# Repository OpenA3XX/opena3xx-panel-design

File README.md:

# 🛫 OpenA3XX: Panels, 3D Printed Components & Reference Archive
Welcome to the central repository for the OpenA3XX **Airbus cockpit build project**! This repository documents the design, construction, and references for all the cockpit panels and components, including 3D printed parts and photographic material used during development.

---

---

## ✈️ About the Project

As part of a long-term flight simulation setup, I'm building a **home Airbus cockpit replica**, focusing on authenticity, durability, and modularity. This project includes:

- Accurate panel layouts (e.g., ADIRS, FLT-CTL, etc.)
- Reference imagery from real cockpits
- 3D printed components (knobs, switch housings, structural parts)
- Design schematics, templates, and notes from real-world dimensions
- Documentation of tools and techniques used in building panels

This repository serves as a **knowledge base** and a **design vault** for other sim builders and enthusiasts who are building or planning to build their own Airbus home cockpit.

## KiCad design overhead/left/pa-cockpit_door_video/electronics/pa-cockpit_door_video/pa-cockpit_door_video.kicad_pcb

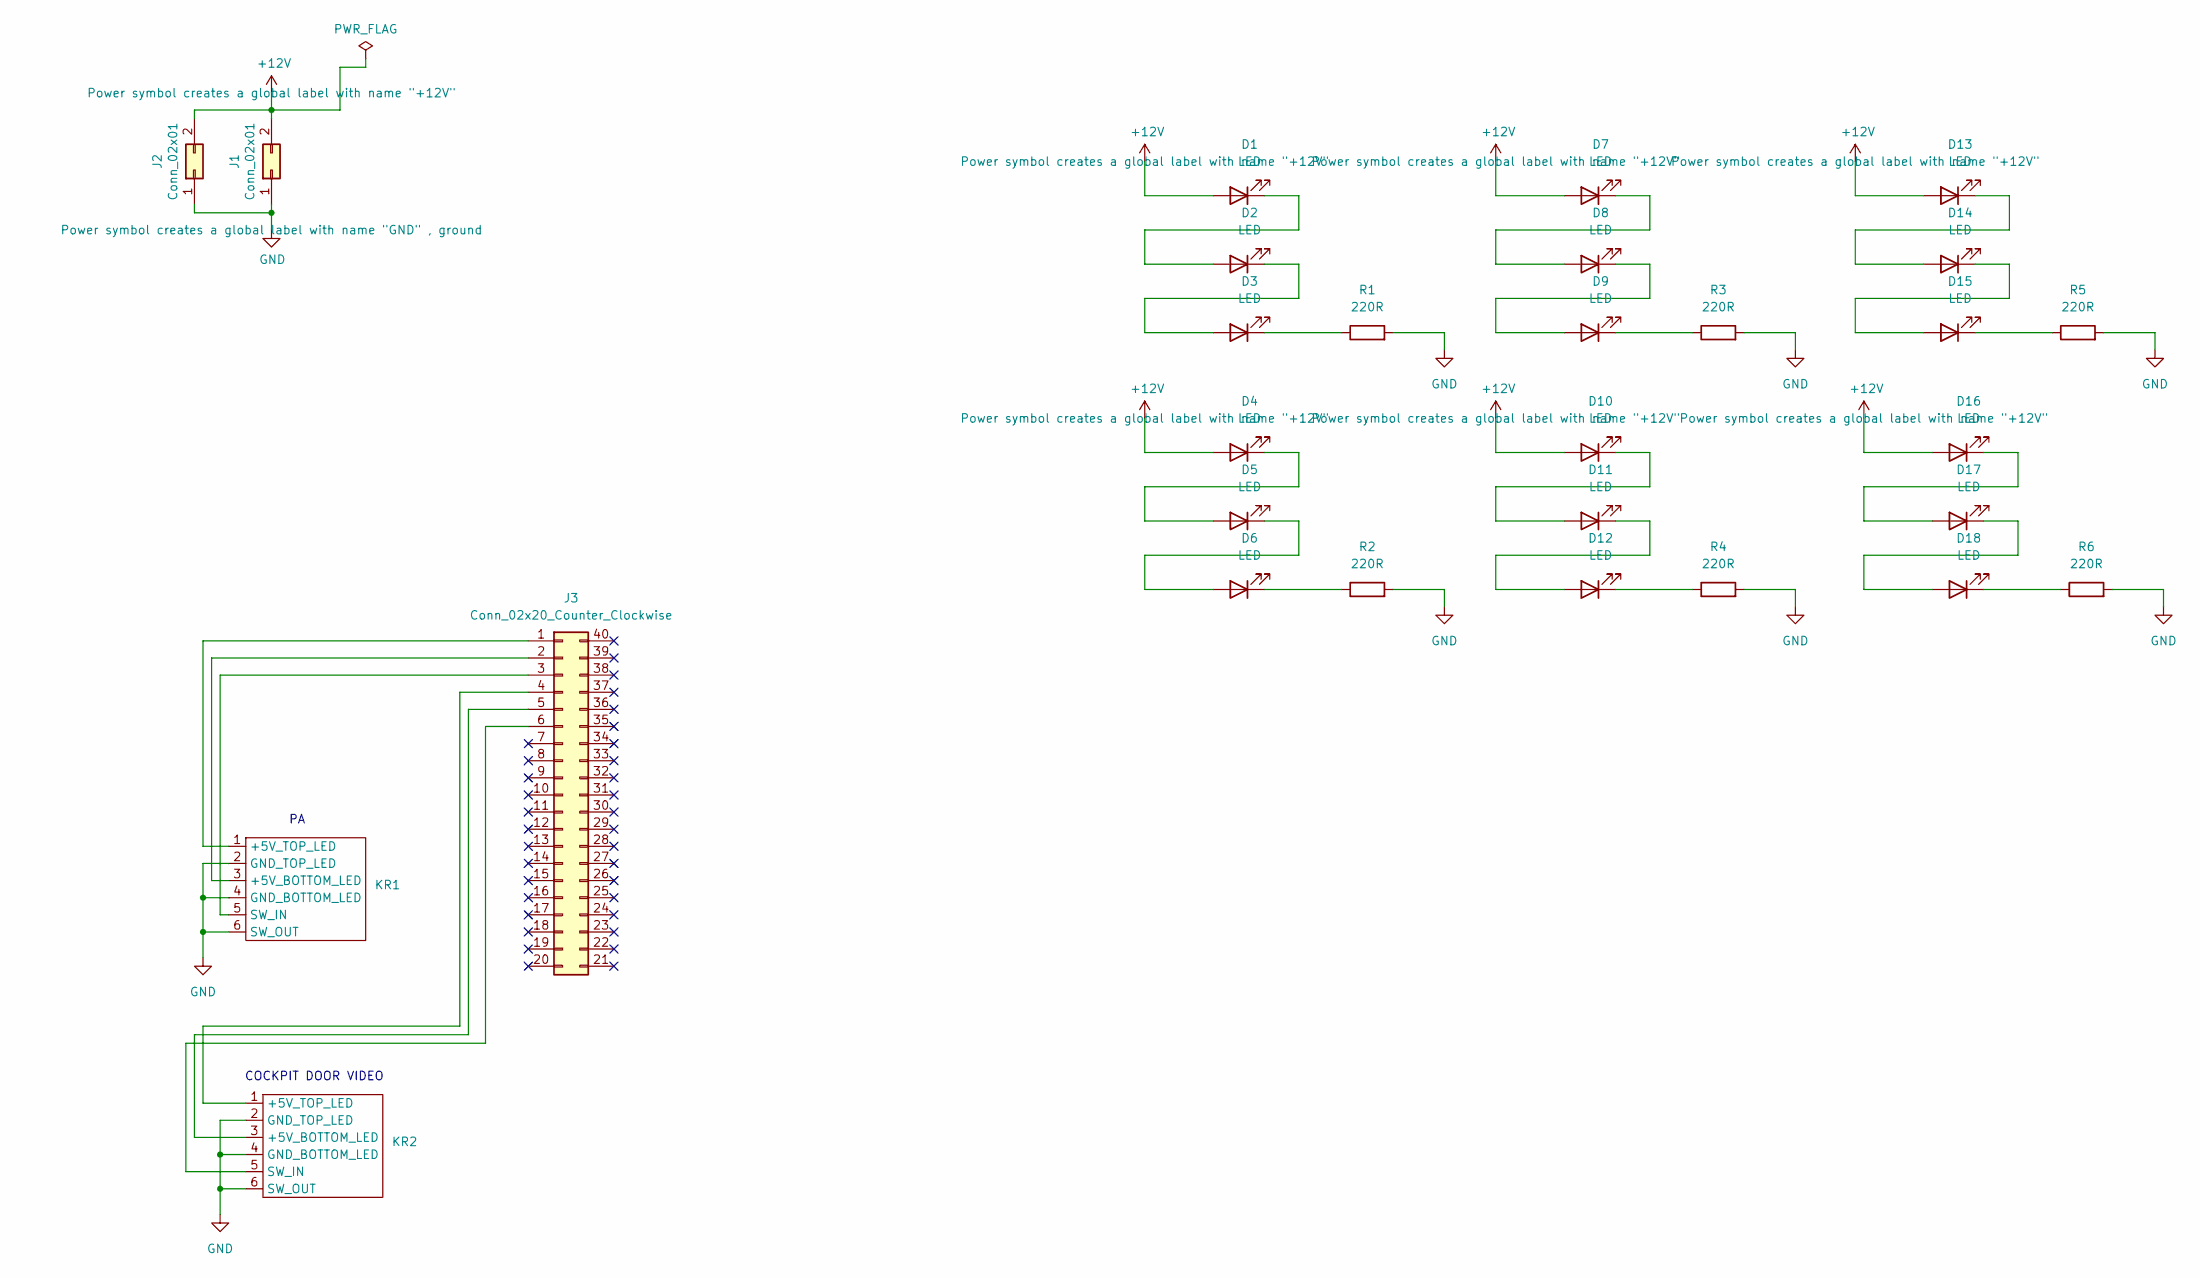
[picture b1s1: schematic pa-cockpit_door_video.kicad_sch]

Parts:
D1, D2, D3, D4, D5, D6, D7, D8, D9, D10, D11, D12, D13, D14, D15, D16, D17, D18: LED; LED_Everlight-SMD3528_3.5x2.8mm_67-21ST
J1, J2: Conn_02x01; TerminalBlock_bornier-2_P5.08mm
J3: Conn_02x20_Counter_Clockwise; PinHeader_2x20_P2.54mm_Vertical
KR1, KR2: Korry Switch
R1, R2, R3, R4, R5, R6: 220R; R_1206_3216Metric_Pad1.30x1.75mm_HandSolder

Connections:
+12V: D1.2 (A), D4.2 (A), D7.2 (A), D10.2 (A), D13.2 (A), D16.2 (A), J1.2, J2.2
GND: J1.1, J2.1, KR1.2 (GND_TOP_LED), KR1.4 (GND_BOTTOM_LED), KR1.6 (SW_OUT), KR2.2 (GND_TOP_LED), KR2.4 (GND_BOTTOM_LED), KR2.6 (SW_OUT), R1.2, R2.2, R3.2, R4.2, R5.2, R6.2
unnamed: D1.1 (K), D2.2 (A)
unnamed: D2.1 (K), D3.2 (A)
unnamed: D3.1 (K), R1.1
unnamed: D4.1 (K), D5.2 (A)
unnamed: D5.1 (K), D6.2 (A)
unnamed: D6.1 (K), R2.1
unnamed: D7.1 (K), D8.2 (A)
unnamed: D8.1 (K), D9.2 (A)
unnamed: D9.1 (K), R3.1
unnamed: D10.1 (K), D11.2 (A)
unnamed: D11.1 (K), D12.2 (A)
unnamed: D12.1 (K), R4.1
unnamed: D13.1 (K), D14.2 (A)
unnamed: D14.1 (K), D15.2 (A)
unnamed: D15.1 (K), R5.1
unnamed: D16.1 (K), D17.2 (A)
unnamed: D17.1 (K), D18.2 (A)
unnamed: D18.1 (K), R6.1
unnamed: J3.1, KR1.1 (+5V_TOP_LED)
unnamed: J3.2, KR1.3 (+5V_BOTTOM_LED)
unnamed: J3.3, KR1.5 (SW_IN)
unnamed: J3.4, KR2.1 (+5V_TOP_LED)
unnamed: J3.5, KR2.3 (+5V_BOTTOM_LED)
unnamed: J3.6, KR2.5 (SW_IN)

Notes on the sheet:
COCKPIT DOOR VIDEO

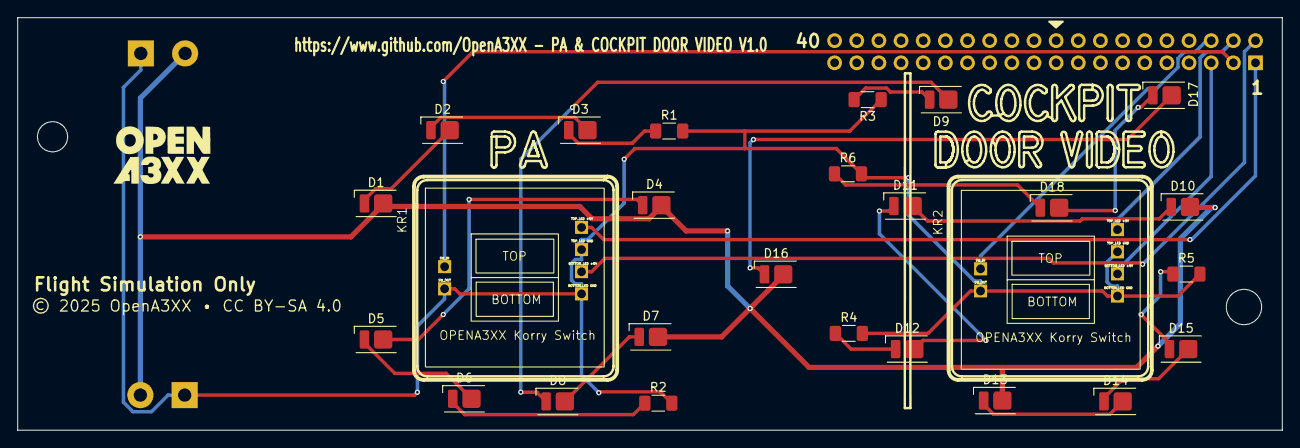
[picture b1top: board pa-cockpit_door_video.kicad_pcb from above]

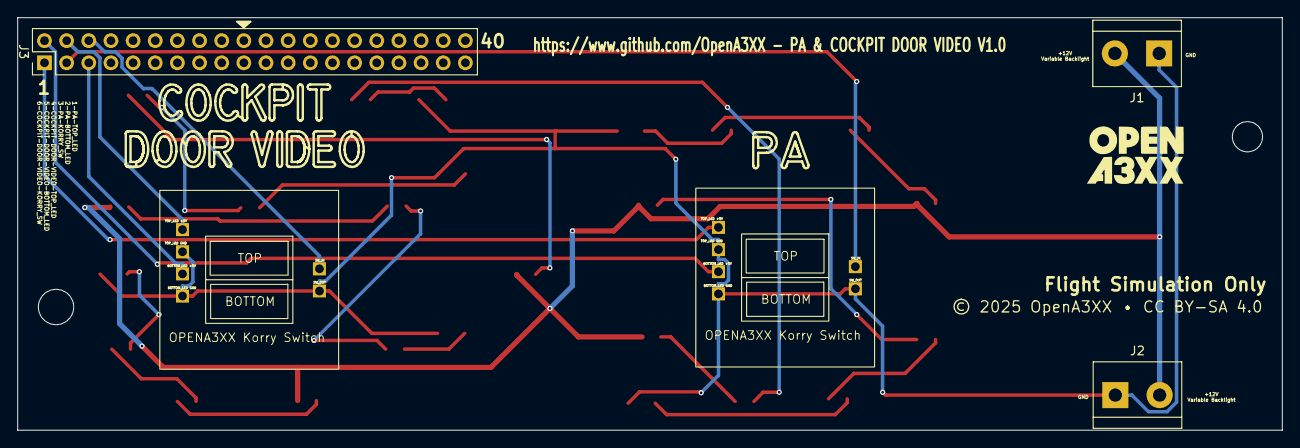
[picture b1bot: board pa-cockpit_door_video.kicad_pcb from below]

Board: 2 copper layers, 145.0 x 47.3 mm, 31 parts (4 on the bottom side), 26 nets.

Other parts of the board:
bottom: LOGO; OpenA3XXLogoSmall
top: LOGO; OpenA3XXLogoSmall

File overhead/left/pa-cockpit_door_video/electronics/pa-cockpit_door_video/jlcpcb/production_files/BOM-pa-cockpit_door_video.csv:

Comment,Designator,Footprint,LCSC,Quantity
LED,"D1,D10,D11,D12,D13,D14,D15,D16,D17,D18,D2,D3,D4,D5,D6,D7,D8,D9",LED_Everlight-SMD3528_3.5x2.8mm_67-21ST,C2843803,18
220R,"R1,R2,R3,R4,R5,R6",R_1206_3216Metric_Pad1.30x1.75mm_HandSolder,C2933785,6
Conn_02x01,"J1,J2",TerminalBlock_bornier-2_P5.08mm,C592976,2
Conn_02x20_Counter_Clockwise,J3,PinHeader_2x20_P2.54mm_Vertical,C725892,1
~,KR2,Korry Switch,,1
~,KR1,Korry Switch,,1

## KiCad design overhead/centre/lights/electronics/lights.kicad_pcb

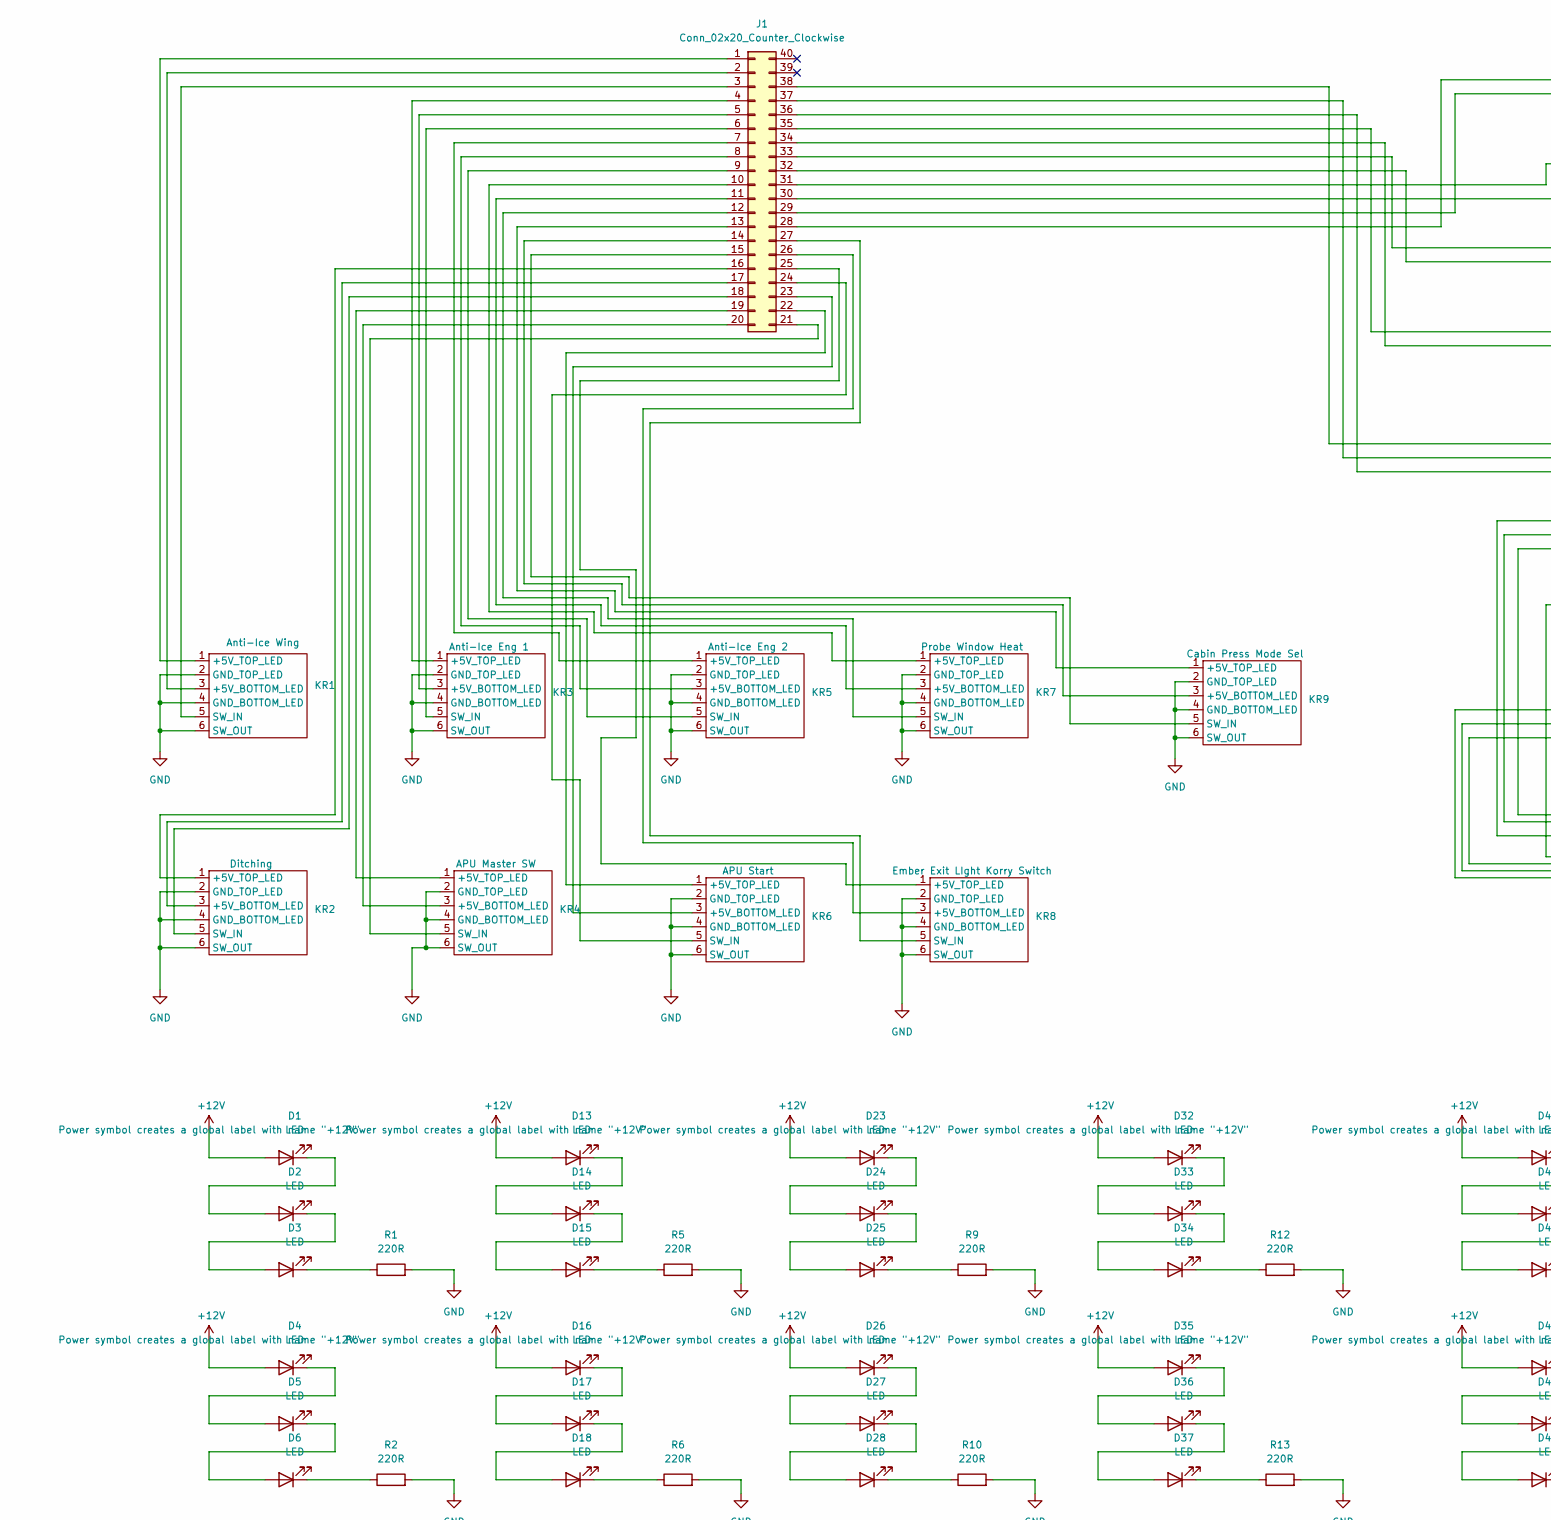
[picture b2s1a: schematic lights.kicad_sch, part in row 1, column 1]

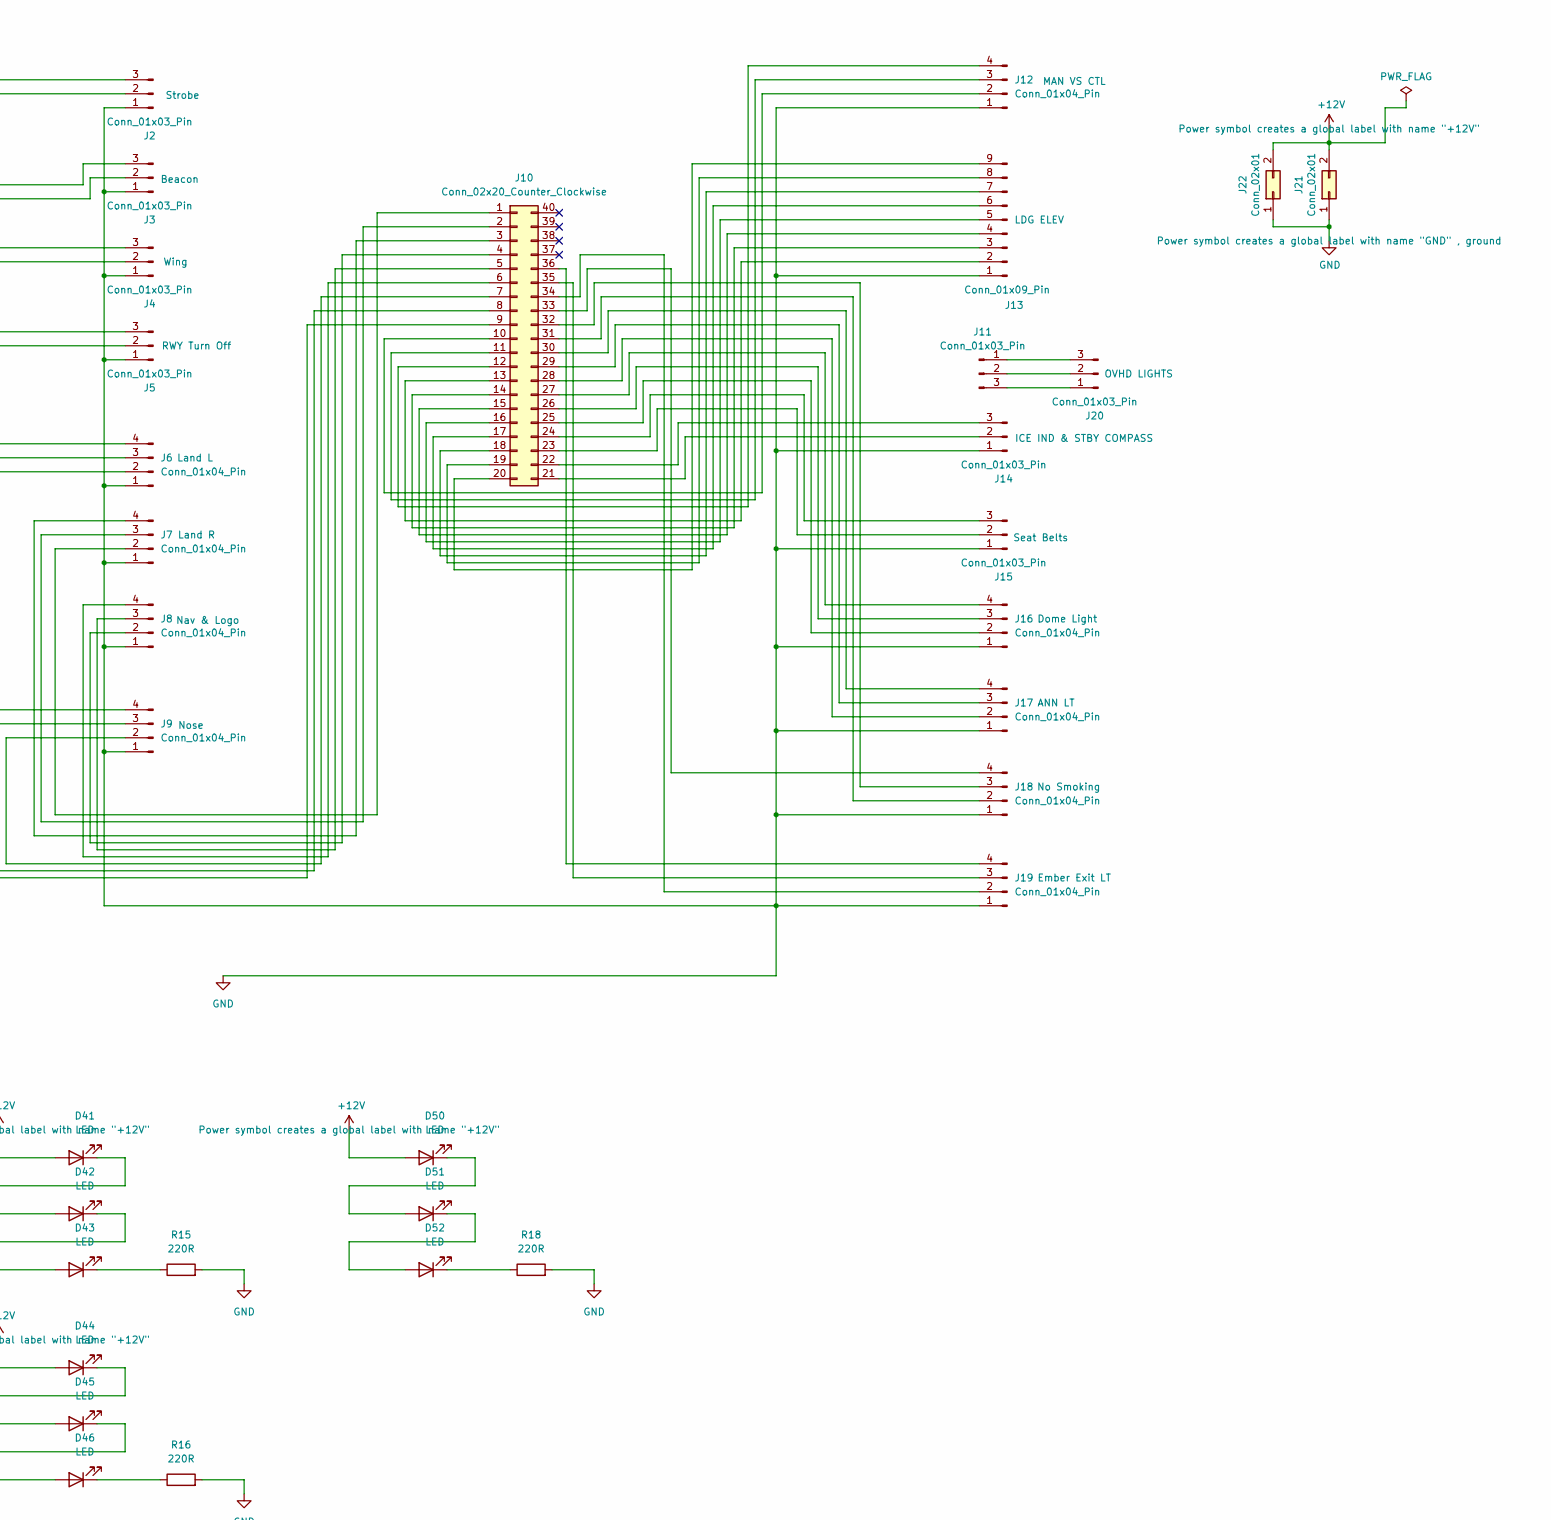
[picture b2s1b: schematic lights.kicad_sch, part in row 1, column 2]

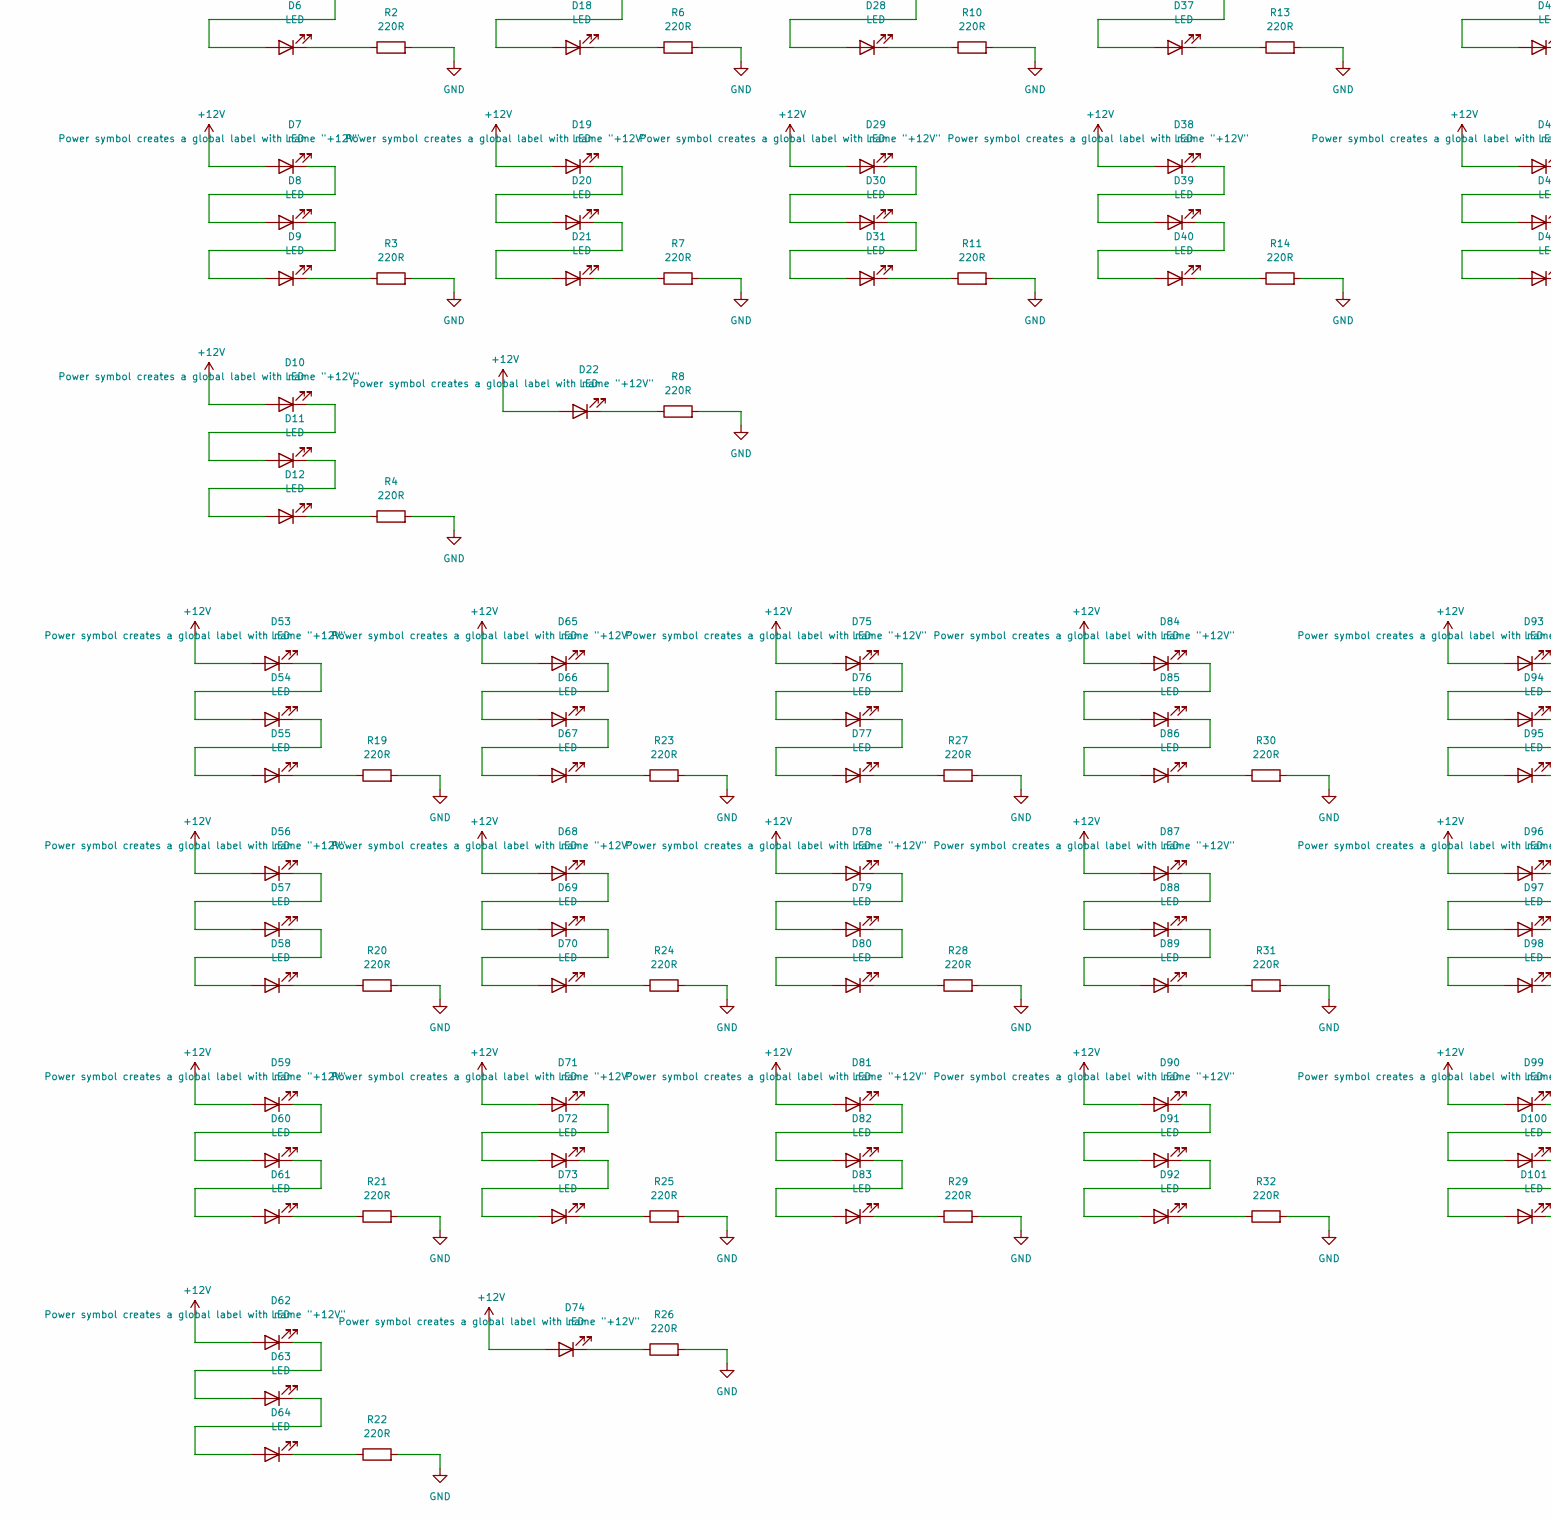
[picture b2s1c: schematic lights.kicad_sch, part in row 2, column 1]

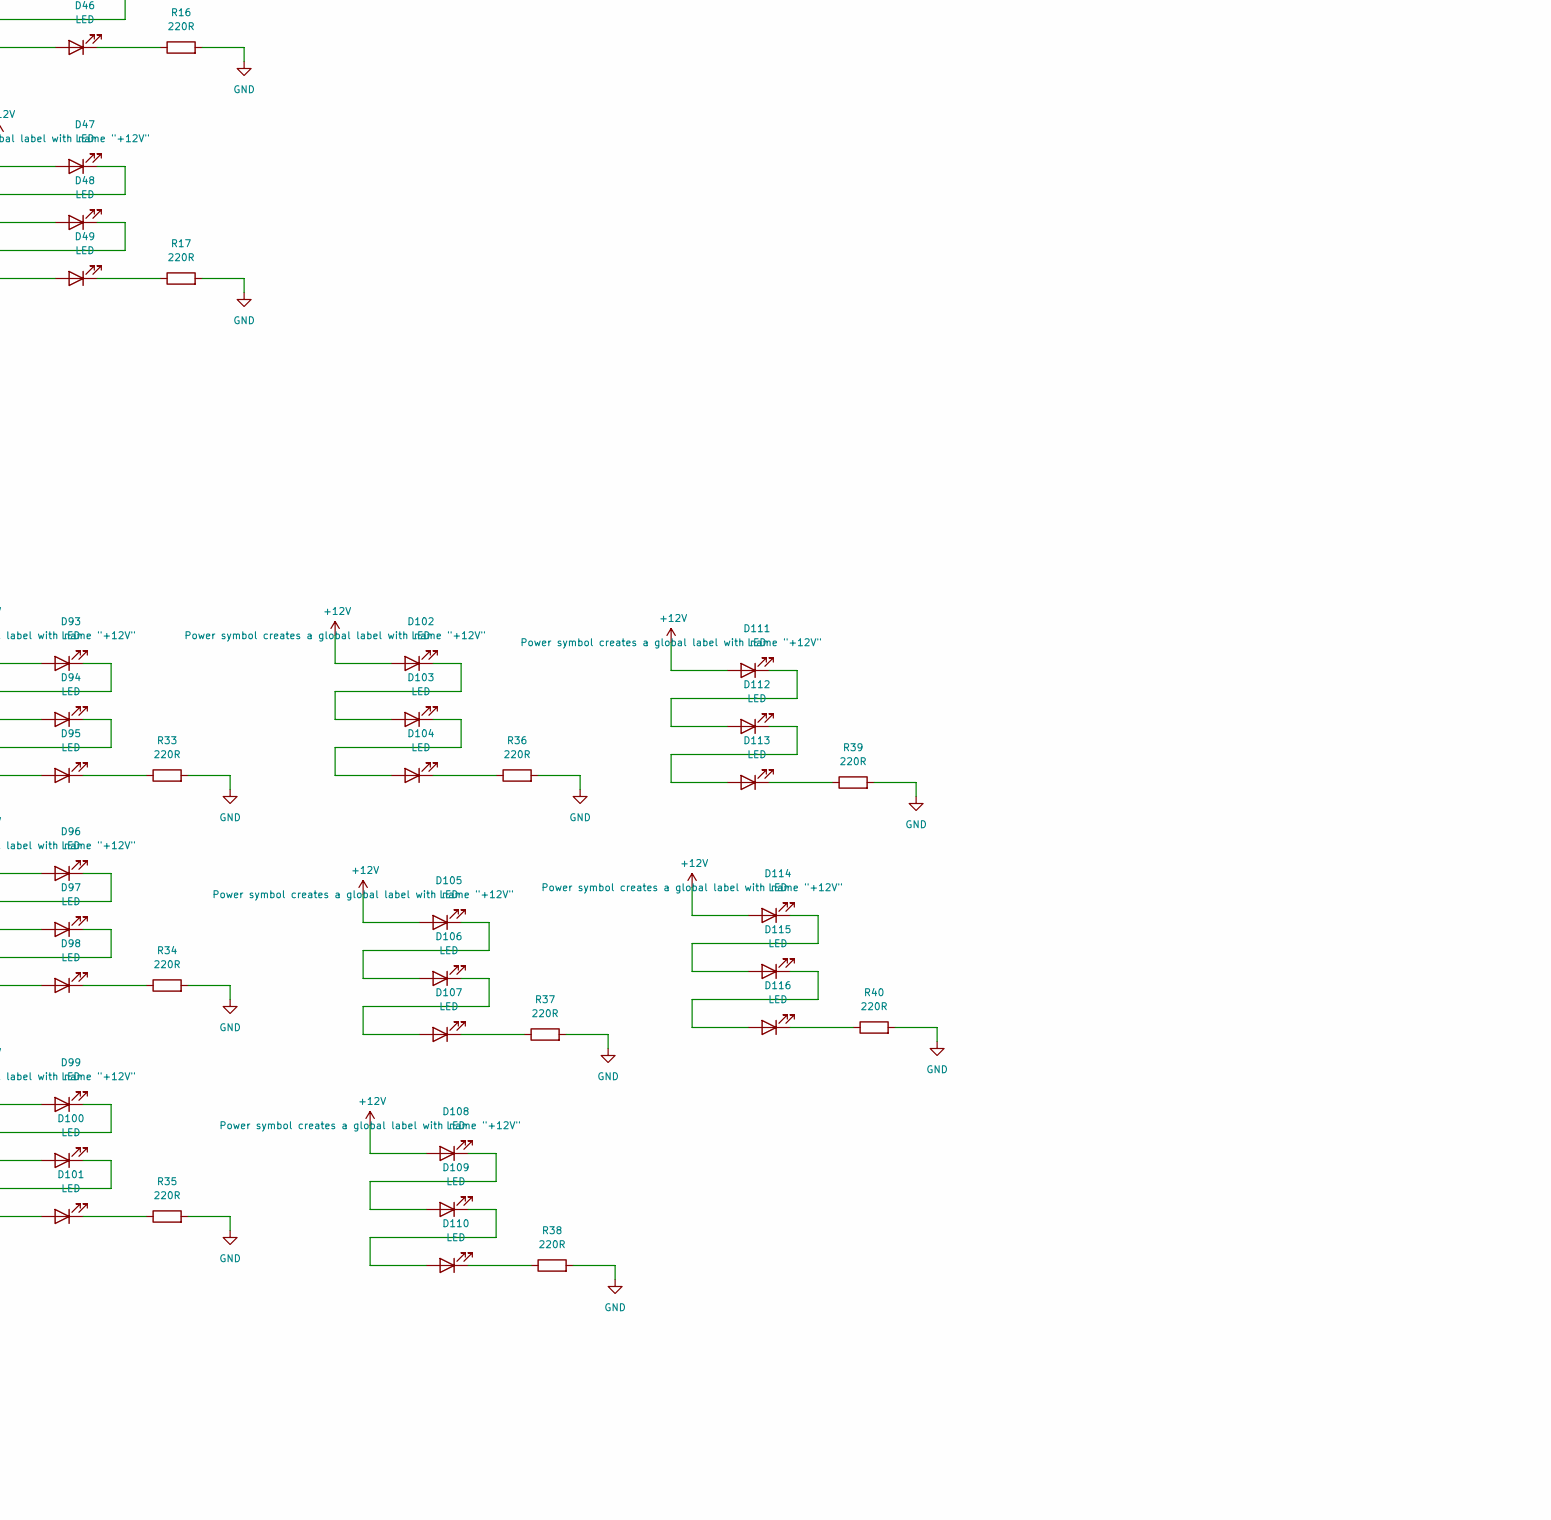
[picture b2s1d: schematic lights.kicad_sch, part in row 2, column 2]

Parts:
D1, D2, D3, D4, D5, D6, D7, D8, D9, D10, D11, D12, D13, D14, D15, D16, D17, D18, D19, D20, D21, D22, D23, D24, D25, D26, D27, D28, D29, D30, D31, D32, D33, D34, D35, D36, D37, D38, D39, D40, D41, D42, D43, D44, D45, D46, D47, D48, D49, D50, D51, D52, D53, D54, D55, D56, D57, D58, D59, D60, D61, D62, D63, D64, D65, D66, D67, D68, D69, D70, D71, D72, D73, D74, D75, D76, D77, D78, D79, D80, D81, D82, D83, D84, D85, D86, D87, D88, D89, D90, D91, D92, D93, D94, D95, D96, D97, D98, D99, D100, D101, D102, D103, D104, D105, D106, D107, D108, D109, D110, D111, D112, D113, D114, D115, D116: LED; LED_Everlight-SMD3528_3.5x2.8mm_67-21ST
J1, J10: Conn_02x20_Counter_Clockwise; PinHeader_2x20_P2.54mm_Vertical
J2, J3, J4, J5, J11, J14, J15: Conn_01x03_Pin; PinHeader_1x03_P2.54mm_Vertical
J6, J7, J8, J9, J12, J16, J17, J18, J19: Conn_01x04_Pin; PinHeader_1x04_P2.54mm_Vertical
J13: Conn_01x09_Pin; PinHeader_1x09_P2.54mm_Vertical
J20: Conn_01x03_Pin; TerminalBlock_bornier-3_P5.08mm
J21, J22: Conn_02x01; TerminalBlock_bornier-2_P5.08mm
KR1, KR2, KR3, KR4, KR5, KR6, KR7, KR8, KR9: Korry Switch
R1, R2, R3, R4, R5, R6, R7, R8, R9, R10, R11, R12, R13, R14, R15, R16, R17, R18, R19, R20, R21, R22, R23, R24, R25, R26, R27, R28, R29, R30, R31, R32, R33, R34, R35, R36, R37, R38, R39, R40: 220R; R_1206_3216Metric_Pad1.30x1.75mm_HandSolder

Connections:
+12V: D1.2 (A), D4.2 (A), D7.2 (A), D10.2 (A), D13.2 (A), D16.2 (A), D19.2 (A), D22.2 (A), D23.2 (A), D26.2 (A), D29.2 (A), D32.2 (A), D35.2 (A), D38.2 (A), D41.2 (A), D44.2 (A), D47.2 (A), D50.2 (A), D53.2 (A), D56.2 (A), D59.2 (A), D62.2 (A), D65.2 (A), D68.2 (A), D71.2 (A), D74.2 (A), D75.2 (A), D78.2 (A), D81.2 (A), D84.2 (A), D87.2 (A), D90.2 (A), D93.2 (A), D96.2 (A), D99.2 (A), D102.2 (A), D105.2 (A), D108.2 (A), D111.2 (A), D114.2 (A), J21.2, J22.2
GND: J2.1, J3.1, J4.1, J5.1, J6.1, J7.1, J8.1, J9.1, J12.1, J13.1, J14.1, J15.1, J16.1, J17.1, J18.1, J19.1, J21.1, J22.1, KR1.2 (GND_TOP_LED), KR1.4 (GND_BOTTOM_LED), KR1.6 (SW_OUT), KR2.2 (GND_TOP_LED), KR2.4 (GND_BOTTOM_LED), KR2.6 (SW_OUT), KR3.2 (GND_TOP_LED), KR3.4 (GND_BOTTOM_LED), KR3.6 (SW_OUT), KR4.2 (GND_TOP_LED), KR4.4 (GND_BOTTOM_LED), KR4.6 (SW_OUT), KR5.2 (GND_TOP_LED), KR5.4 (GND_BOTTOM_LED), KR5.6 (SW_OUT), KR6.2 (GND_TOP_LED), KR6.4 (GND_BOTTOM_LED), KR6.6 (SW_OUT), KR7.2 (GND_TOP_LED), KR7.4 (GND_BOTTOM_LED), KR7.6 (SW_OUT), KR8.2 (GND_TOP_LED), KR8.4 (GND_BOTTOM_LED), KR8.6 (SW_OUT), KR9.2 (GND_TOP_LED), KR9.4 (GND_BOTTOM_LED), KR9.6 (SW_OUT), R1.2, R2.2, R3.2, R4.2, R5.2, R6.2, R7.2, R8.2, R9.2, R10.2, R11.2, R12.2, R13.2, R14.2, R15.2, R16.2, R17.2, R18.2, R19.2, R20.2, R21.2, R22.2, R23.2, R24.2, R25.2, R26.2, R27.2, R28.2, R29.2, R30.2, R31.2, R32.2, R33.2, R34.2, R35.2, R36.2, R37.2, R38.2, R39.2, R40.2
unnamed: D1.1 (K), D2.2 (A)
unnamed: D2.1 (K), D3.2 (A)
unnamed: D3.1 (K), R1.1
unnamed: D4.1 (K), D5.2 (A)
unnamed: D5.1 (K), D6.2 (A)
unnamed: D6.1 (K), R2.1
unnamed: D7.1 (K), D8.2 (A)
unnamed: D8.1 (K), D9.2 (A)
unnamed: D9.1 (K), R3.1
unnamed: D10.1 (K), D11.2 (A)
unnamed: D11.1 (K), D12.2 (A)
unnamed: D12.1 (K), R4.1
unnamed: D13.1 (K), D14.2 (A)
unnamed: D14.1 (K), D15.2 (A)
unnamed: D15.1 (K), R5.1
unnamed: D16.1 (K), D17.2 (A)
unnamed: D17.1 (K), D18.2 (A)
unnamed: D18.1 (K), R6.1
unnamed: D19.1 (K), D20.2 (A)
unnamed: D20.1 (K), D21.2 (A)
unnamed: D21.1 (K), R7.1
unnamed: D22.1 (K), R8.1
unnamed: D23.1 (K), D24.2 (A)
unnamed: D24.1 (K), D25.2 (A)
unnamed: D25.1 (K), R9.1
unnamed: D26.1 (K), D27.2 (A)
unnamed: D27.1 (K), D28.2 (A)
unnamed: D28.1 (K), R10.1
unnamed: D29.1 (K), D30.2 (A)
unnamed: D30.1 (K), D31.2 (A)
unnamed: D31.1 (K), R11.1
unnamed: D32.1 (K), D33.2 (A)
unnamed: D33.1 (K), D34.2 (A)
unnamed: D34.1 (K), R12.1
unnamed: D35.1 (K), D36.2 (A)
unnamed: D36.1 (K), D37.2 (A)
unnamed: D37.1 (K), R13.1
unnamed: D38.1 (K), D39.2 (A)
unnamed: D39.1 (K), D40.2 (A)
unnamed: D40.1 (K), R14.1
unnamed: D41.1 (K), D42.2 (A)
unnamed: D42.1 (K), D43.2 (A)
unnamed: D43.1 (K), R15.1
unnamed: D44.1 (K), D45.2 (A)
unnamed: D45.1 (K), D46.2 (A)
unnamed: D46.1 (K), R16.1
unnamed: D47.1 (K), D48.2 (A)
unnamed: D48.1 (K), D49.2 (A)
unnamed: D49.1 (K), R17.1
unnamed: D50.1 (K), D51.2 (A)
unnamed: D51.1 (K), D52.2 (A)
unnamed: D52.1 (K), R18.1
unnamed: D53.1 (K), D54.2 (A)
unnamed: D54.1 (K), D55.2 (A)
unnamed: D55.1 (K), R19.1
unnamed: D56.1 (K), D57.2 (A)
unnamed: D57.1 (K), D58.2 (A)
unnamed: D58.1 (K), R20.1
unnamed: D59.1 (K), D60.2 (A)
unnamed: D60.1 (K), D61.2 (A)
unnamed: D61.1 (K), R21.1
unnamed: D62.1 (K), D63.2 (A)
unnamed: D63.1 (K), D64.2 (A)
unnamed: D64.1 (K), R22.1
unnamed: D65.1 (K), D66.2 (A)
unnamed: D66.1 (K), D67.2 (A)
unnamed: D67.1 (K), R23.1
unnamed: D68.1 (K), D69.2 (A)
unnamed: D69.1 (K), D70.2 (A)
unnamed: D70.1 (K), R24.1
unnamed: D71.1 (K), D72.2 (A)
unnamed: D72.1 (K), D73.2 (A)
unnamed: D73.1 (K), R25.1
unnamed: D74.1 (K), R26.1
unnamed: D75.1 (K), D76.2 (A)
unnamed: D76.1 (K), D77.2 (A)
unnamed: D77.1 (K), R27.1
unnamed: D78.1 (K), D79.2 (A)
unnamed: D79.1 (K), D80.2 (A)
unnamed: D80.1 (K), R28.1
unnamed: D81.1 (K), D82.2 (A)
unnamed: D82.1 (K), D83.2 (A)
unnamed: D83.1 (K), R29.1
unnamed: D84.1 (K), D85.2 (A)
unnamed: D85.1 (K), D86.2 (A)
unnamed: D86.1 (K), R30.1
unnamed: D87.1 (K), D88.2 (A)
unnamed: D88.1 (K), D89.2 (A)
unnamed: D89.1 (K), R31.1
unnamed: D90.1 (K), D91.2 (A)
unnamed: D91.1 (K), D92.2 (A)
unnamed: D92.1 (K), R32.1
unnamed: D93.1 (K), D94.2 (A)
unnamed: D94.1 (K), D95.2 (A)
unnamed: D95.1 (K), R33.1
unnamed: D96.1 (K), D97.2 (A)
unnamed: D97.1 (K), D98.2 (A)
unnamed: D98.1 (K), R34.1
unnamed: D99.1 (K), D100.2 (A)
unnamed: D100.1 (K), D101.2 (A)
unnamed: D101.1 (K), R35.1
unnamed: D102.1 (K), D103.2 (A)
unnamed: D103.1 (K), D104.2 (A)
unnamed: D104.1 (K), R36.1
unnamed: D105.1 (K), D106.2 (A)
unnamed: D106.1 (K), D107.2 (A)
unnamed: D107.1 (K), R37.1
unnamed: D108.1 (K), D109.2 (A)
unnamed: D109.1 (K), D110.2 (A)
unnamed: D110.1 (K), R38.1
unnamed: D111.1 (K), D112.2 (A)
unnamed: D112.1 (K), D113.2 (A)
unnamed: D113.1 (K), R39.1
unnamed: D114.1 (K), D115.2 (A)
unnamed: D115.1 (K), D116.2 (A)
unnamed: D116.1 (K), R40.1
unnamed: J1.1, KR1.1 (+5V_TOP_LED)
unnamed: J1.2, KR1.3 (+5V_BOTTOM_LED)
unnamed: J1.3, KR1.5 (SW_IN)
unnamed: J1.4, KR3.1 (+5V_TOP_LED)
unnamed: J1.5, KR3.3 (+5V_BOTTOM_LED)
unnamed: J1.6, KR3.5 (SW_IN)
unnamed: J1.7, KR5.1 (+5V_TOP_LED)
unnamed: J1.8, KR5.3 (+5V_BOTTOM_LED)
unnamed: J1.9, KR5.5 (SW_IN)
unnamed: J1.10, KR7.1 (+5V_TOP_LED)
unnamed: J1.11, KR7.3 (+5V_BOTTOM_LED)
unnamed: J1.12, KR7.5 (SW_IN)
unnamed: J1.13, KR9.1 (+5V_TOP_LED)
unnamed: J1.14, KR9.3 (+5V_BOTTOM_LED)
unnamed: J1.15, KR9.5 (SW_IN)
unnamed: J1.16, KR2.1 (+5V_TOP_LED)
unnamed: J1.17, KR2.3 (+5V_BOTTOM_LED)
unnamed: J1.18, KR2.5 (SW_IN)
unnamed: J1.19, KR4.1 (+5V_TOP_LED)
unnamed: J1.20, KR4.3 (+5V_BOTTOM_LED)
unnamed: J1.21, KR4.5 (SW_IN)
unnamed: J1.22, KR6.1 (+5V_TOP_LED)
unnamed: J1.23, KR6.3 (+5V_BOTTOM_LED)
unnamed: J1.26, KR8.3 (+5V_BOTTOM_LED)
unnamed: J1.27, KR8.5 (SW_IN)
unnamed: J1.28, J2.3
unnamed: J1.29, J2.2
unnamed: J1.30, J3.2
unnamed: J1.31, J3.3
unnamed: J1.32, J4.2
unnamed: J1.33, J4.3
unnamed: J1.34, J5.2
unnamed: J1.35, J5.3
unnamed: J1.36, J6.2
unnamed: J1.37, J6.3
unnamed: J1.38, J6.4
unnamed: J7.2, J10.1
unnamed: J7.3, J10.2
unnamed: J7.4, J10.3
unnamed: J8.2, J10.4
unnamed: J8.3, J10.5
unnamed: J8.4, J10.6
unnamed: J9.2, J10.7
unnamed: J9.3, J10.8
unnamed: J9.4, J10.9
unnamed: J10.10, J12.2
unnamed: J10.11, J12.3
unnamed: J10.12, J12.4
unnamed: J10.13, J13.2
unnamed: J10.14, J13.3
unnamed: J10.15, J13.4
unnamed: J10.16, J13.5
unnamed: J10.17, J13.6
unnamed: J10.18, J13.7
unnamed: J10.19, J13.8
unnamed: J10.20, J13.9
unnamed: J10.21, J14.2
unnamed: J10.22, J14.3
unnamed: J10.23, J15.2
unnamed: J10.24, J15.3
unnamed: J10.25, J16.2
unnamed: J10.26, J16.3
unnamed: J10.27, J16.4
unnamed: J10.28, J17.2
unnamed: J10.29, J17.3
unnamed: J10.30, J17.4
unnamed: J10.31, J18.2
unnamed: J10.32, J18.3
unnamed: J10.33, J18.4
unnamed: J10.34, J19.2
unnamed: J10.35, J19.3
unnamed: J10.36, J19.4
unnamed: J11.1, J20.3
unnamed: J11.2, J20.2
unnamed: J11.3, J20.1

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
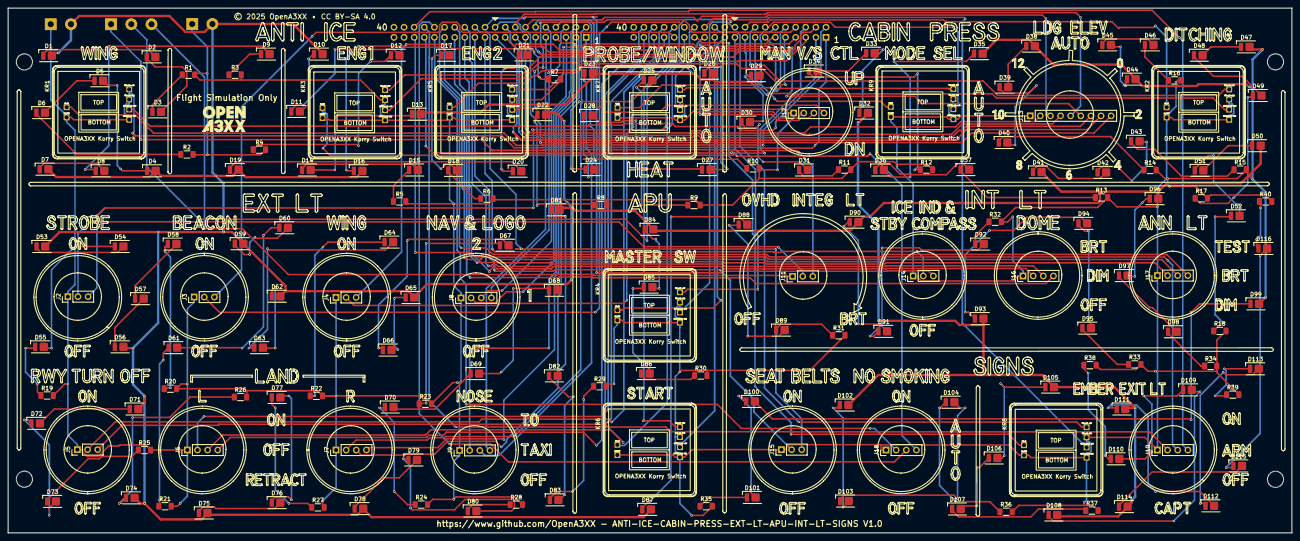
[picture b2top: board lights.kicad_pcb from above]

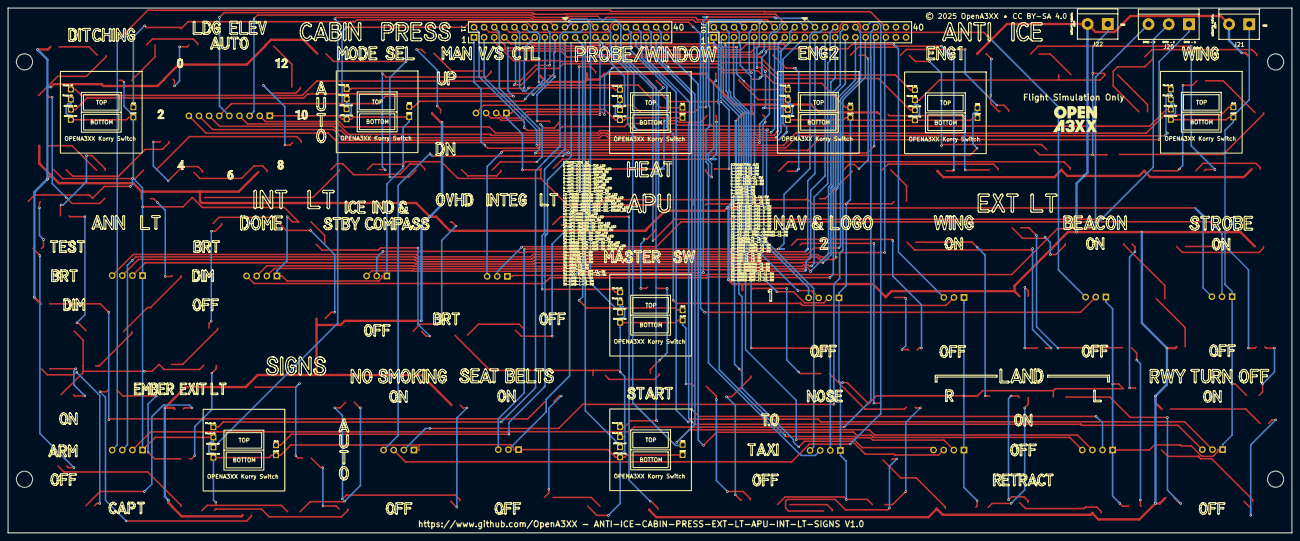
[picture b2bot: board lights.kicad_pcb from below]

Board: 2 copper layers, 322.3 x 131.8 mm, 189 parts (6 on the bottom side), 195 nets.

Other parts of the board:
bottom: LOGO; OpenA3XXLogoSmall
top: LOGO; OpenA3XXLogoSmall

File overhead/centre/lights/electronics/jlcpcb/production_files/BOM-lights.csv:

Comment,Designator,Footprint,LCSC,Quantity
Conn_01x09_Pin,J13,PinHeader_1x09_P2.54mm_Vertical,C225484,1
LED,"D1,D10,D100,D101,D102,D103,D104,D105,D106,D107,D108,D109,D11,D110,D111,D112,D113,D114,D115,D116,D12,D13,D14,D15,D16,D17,D18,D19,D2,D20,D21,D22,D23,D24,D25,D26,D27,D28,D29,D3,D30,D31,D32,D33,D34,D35,D36,D37,D38,D39,D4,D40,D41,D42,D43,D44,D45,D46,D47,D48,D49,D5,D50,D51,D52,D53,D54,D55,D56,D57,D58,D59,D6,D60,D61,D62,D63,D64,D65,D66,D67,D68,D69,D7,D70,D71,D72,D73,D74,D75,D76,D77,D78,D79,D8,D80,D81,D82,D83,D84,D85,D86,D87,D88,D89,D9,D90,D91,D92,D93,D94,D95,D96,D97,D98,D99",LED_Everlight-SMD3528_3.5x2.8mm_67-21ST,C2843803,116
220R,"R1,R10,R11,R12,R13,R14,R15,R16,R17,R18,R19,R2,R20,R21,R22,R23,R24,R25,R26,R27,R28,R29,R3,R30,R31,R32,R33,R34,R35,R36,R37,R38,R39,R4,R40,R5,R6,R7,R8,R9",R_1206_3216Metric_Pad1.30x1.75mm_HandSolder,C2933785,40
Conn_01x04_Pin,"J12,J16,J17,J18,J19,J6,J7,J8,J9",PinHeader_1x04_P2.54mm_Vertical,C5116483,9
Conn_01x03_Pin,"J11,J14,J15,J2,J3,J4,J5",PinHeader_1x03_P2.54mm_Vertical,C5445396,7
Conn_01x03_Pin,J20,TerminalBlock_bornier-3_P5.08mm,C589616,1
Conn_02x01,"J21,J22",TerminalBlock_bornier-2_P5.08mm,C592976,2
Conn_02x20_Counter_Clockwise,"J1,J10",PinHeader_2x20_P2.54mm_Vertical,C725892,2
~,KR3,Korry Switch,,1
~,KR9,Korry Switch,,1
~,KR2,Korry Switch,,1
~,KR6,Korry Switch,,1
~,KR7,Korry Switch,,1
~,KR8,Korry Switch,,1
~,KR4,Korry Switch,,1
~,KR1,Korry Switch,,1
~,KR5,Korry Switch,,1

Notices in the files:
overhead/centre/elec/electronics/elec.kicad_pcb:
© 2025 OpenA3XX • CC BY-SA 4.0
